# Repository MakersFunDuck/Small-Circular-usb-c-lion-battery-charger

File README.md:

A compact USB-C Li-ion battery charger designed for the Parkside Electric Precision Screwdriver.

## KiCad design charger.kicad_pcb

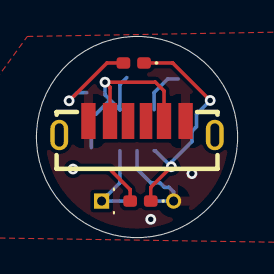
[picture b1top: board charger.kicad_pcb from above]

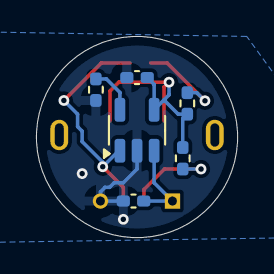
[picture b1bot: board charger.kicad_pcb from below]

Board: 2 copper layers, 11.2 x 11.2 mm, 10 parts (6 on the bottom side), 7 nets.

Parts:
BT1: lion; PinHeader_1x03_P1.00mm_Vertical
C1, C2: 1uF; C_0402_1005Metric_Pad0.74x0.62mm_HandSolder
D1, D2: LED; LED_0402_1005Metric_Pad0.77x0.64mm_HandSolder
J1: USB_C_Receptacle_PowerOnly_6P; USB-TYPE-C-SMD_MC-306LS-H65
R1: 1.65k; R_0402_1005Metric_Pad0.72x0.64mm_HandSolder
R2, R3: 300Ω; R_0402_1005Metric_Pad0.72x0.64mm_HandSolder
U1: LTC4054XES5-4.2; TSOT-23-5

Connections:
+5V: C1.1, J1.A9 (VBUS), J1.B9 (VBUS), R2.1, R3.1, U1.4 (V_{CC})
GND: BT1.2 (-), C1.2, C2.2, J1.A12 (GND), J1.B12 (GND), R1.2, U1.2 (GND)
unnamed: BT1.1 (+), C2.1, U1.3 (BAT)
unnamed: D1.2 (A), R3.2
unnamed: D1.1 (K), D2.1 (K), U1.1 (~CHRG)
unnamed: D2.2 (A), R2.2
unnamed: R1.1, U1.5 (PROG)
